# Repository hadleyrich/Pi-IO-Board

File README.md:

Pi IO Board
===========
Copyright 2013 nice technology Ltd  
Website: <http://nicegear.co/pi-io-board>

The Pi IO Board is a small PCB allowing you to break out all the GPIO
pins on the Raspberry Pi onto a breadboard.

Features:

 * Allows you to utilise the Raspberry Pi GPIO pins on a breadboard.

LICENSE
-------
Licensed under the TAPR Open Hardware License (www.tapr.org/OHL).
See the "LICENSE" file within this repository for the full license
in plain text format.

INSTALLATION
------------
The design is saved as an EAGLE project. EAGLE PCB design software is
available from www.cadsoftusa.com free for non-commercial use. To use
this project download it and place the directory containing these files
into the "eagle" directory on your computer. Then open EAGLE and
navigate to Projects -> eagle -> Pi-IO-Board.

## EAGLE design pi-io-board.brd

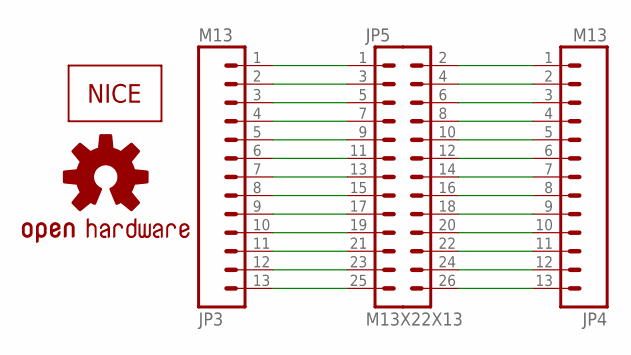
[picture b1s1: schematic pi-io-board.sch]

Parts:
JP3, JP4: M13; 1X13
JP5: M13X22X13; 2X13
LOGO1: OSHW-LOGOS; OSHW-LOGO-S
U$1: NICE-LOGO04; NICE-LOGO-04

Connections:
unnamed: JP3.1, JP5.1
unnamed: JP3.2, JP5.3
unnamed: JP3.3, JP5.5
unnamed: JP3.4, JP5.7
unnamed: JP3.5, JP5.9
unnamed: JP3.6, JP5.11
unnamed: JP3.7, JP5.13
unnamed: JP3.8, JP5.15
unnamed: JP3.9, JP5.17
unnamed: JP3.10, JP5.19
unnamed: JP3.11, JP5.21
unnamed: JP3.12, JP5.23
unnamed: JP3.13, JP5.25
unnamed: JP4.1, JP5.2
unnamed: JP4.2, JP5.4
unnamed: JP4.3, JP5.6
unnamed: JP4.4, JP5.8
unnamed: JP4.5, JP5.10
unnamed: JP4.6, JP5.12
unnamed: JP4.7, JP5.14
unnamed: JP4.8, JP5.16
unnamed: JP4.9, JP5.18
unnamed: JP4.10, JP5.20
unnamed: JP4.11, JP5.22
unnamed: JP4.12, JP5.24
unnamed: JP4.13, JP5.26

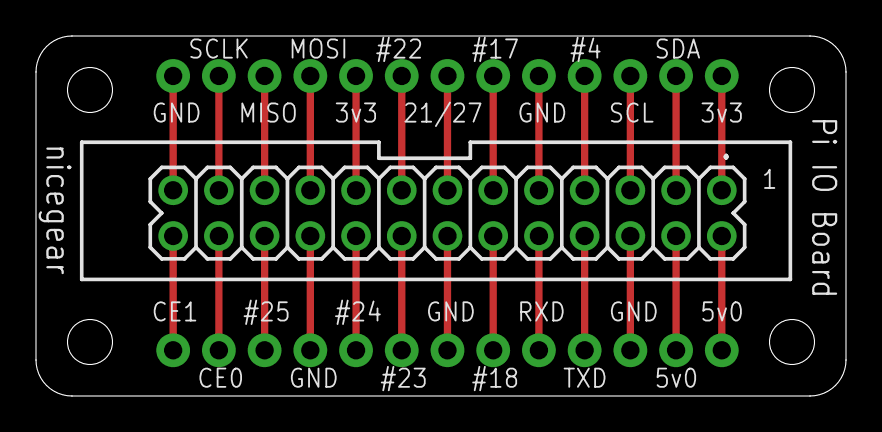
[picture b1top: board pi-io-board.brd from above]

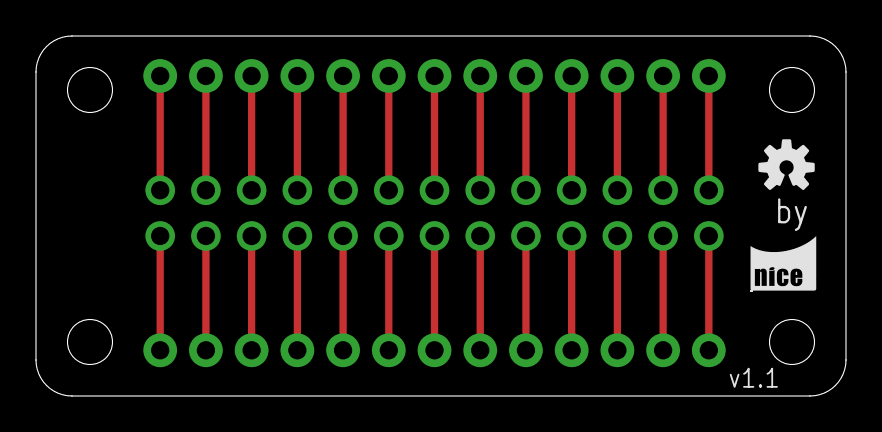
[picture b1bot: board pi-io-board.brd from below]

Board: 2 copper layers, 45.0 x 20.0 mm, 5 parts (2 on the bottom side), 26 nets.

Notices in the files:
parts and their libraries:
SparkFun-Connectors: Licensing: CC v3.0 Share-Alike You are welcome to use this library for commercial purposes.
